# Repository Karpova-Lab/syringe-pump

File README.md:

# !!! Please see an updated version of this pump at https://www.github.com/Karpova-Lab/syringe-pump !!!

# Open Syringe Pump

- Full documentation: [https://karpova-lab.github.io/syringe-pump/v3.0/](https://karpova-lab.github.io/syringe-pump/v3.0/)
- Demo video: [https://vimeo.com/543307158](https://vimeo.com/543307158)
- The design of this pump has been updated to use some 3D printed parts. This results in fewer parts, faster/easier assembly, and a stiffer frame. The previous lasercut-only design is available on this repository's [lasercut_frame branch](https://github.com/Karpova-Lab/syringe-pump/tree/lasercut_frame).

# Features
- Push and pull capable
- Small footprint (33 cm x 14 cm x 10 cm)
- Can be mounted vertically to [DIN rail](https://duckduckgo.com/?q=DIN+rail&t=hc&va=u&iax=images&ia=images)
- Modular electronics can be swapped in and out to be compatible with whatever system you choose
- Cost ~$200
- Assembly time ~15 minutes

## Demo Video

<a target="_blank" href="https://vimeo.com/543307158">
    </img>
</a>

## Diagram

## Render

### Pump
Small footprint operate horizontally or be mounted vertically to DIN rail

<a href="readme_media/vertical_render.gif">
  
  </img>
</a>
<a href="readme_media/iso_views.png">
  
  </img>
</a>

### Modular motor controller
Swap out the motor controller to make upgrades or add compatibility with various systems.

</img>

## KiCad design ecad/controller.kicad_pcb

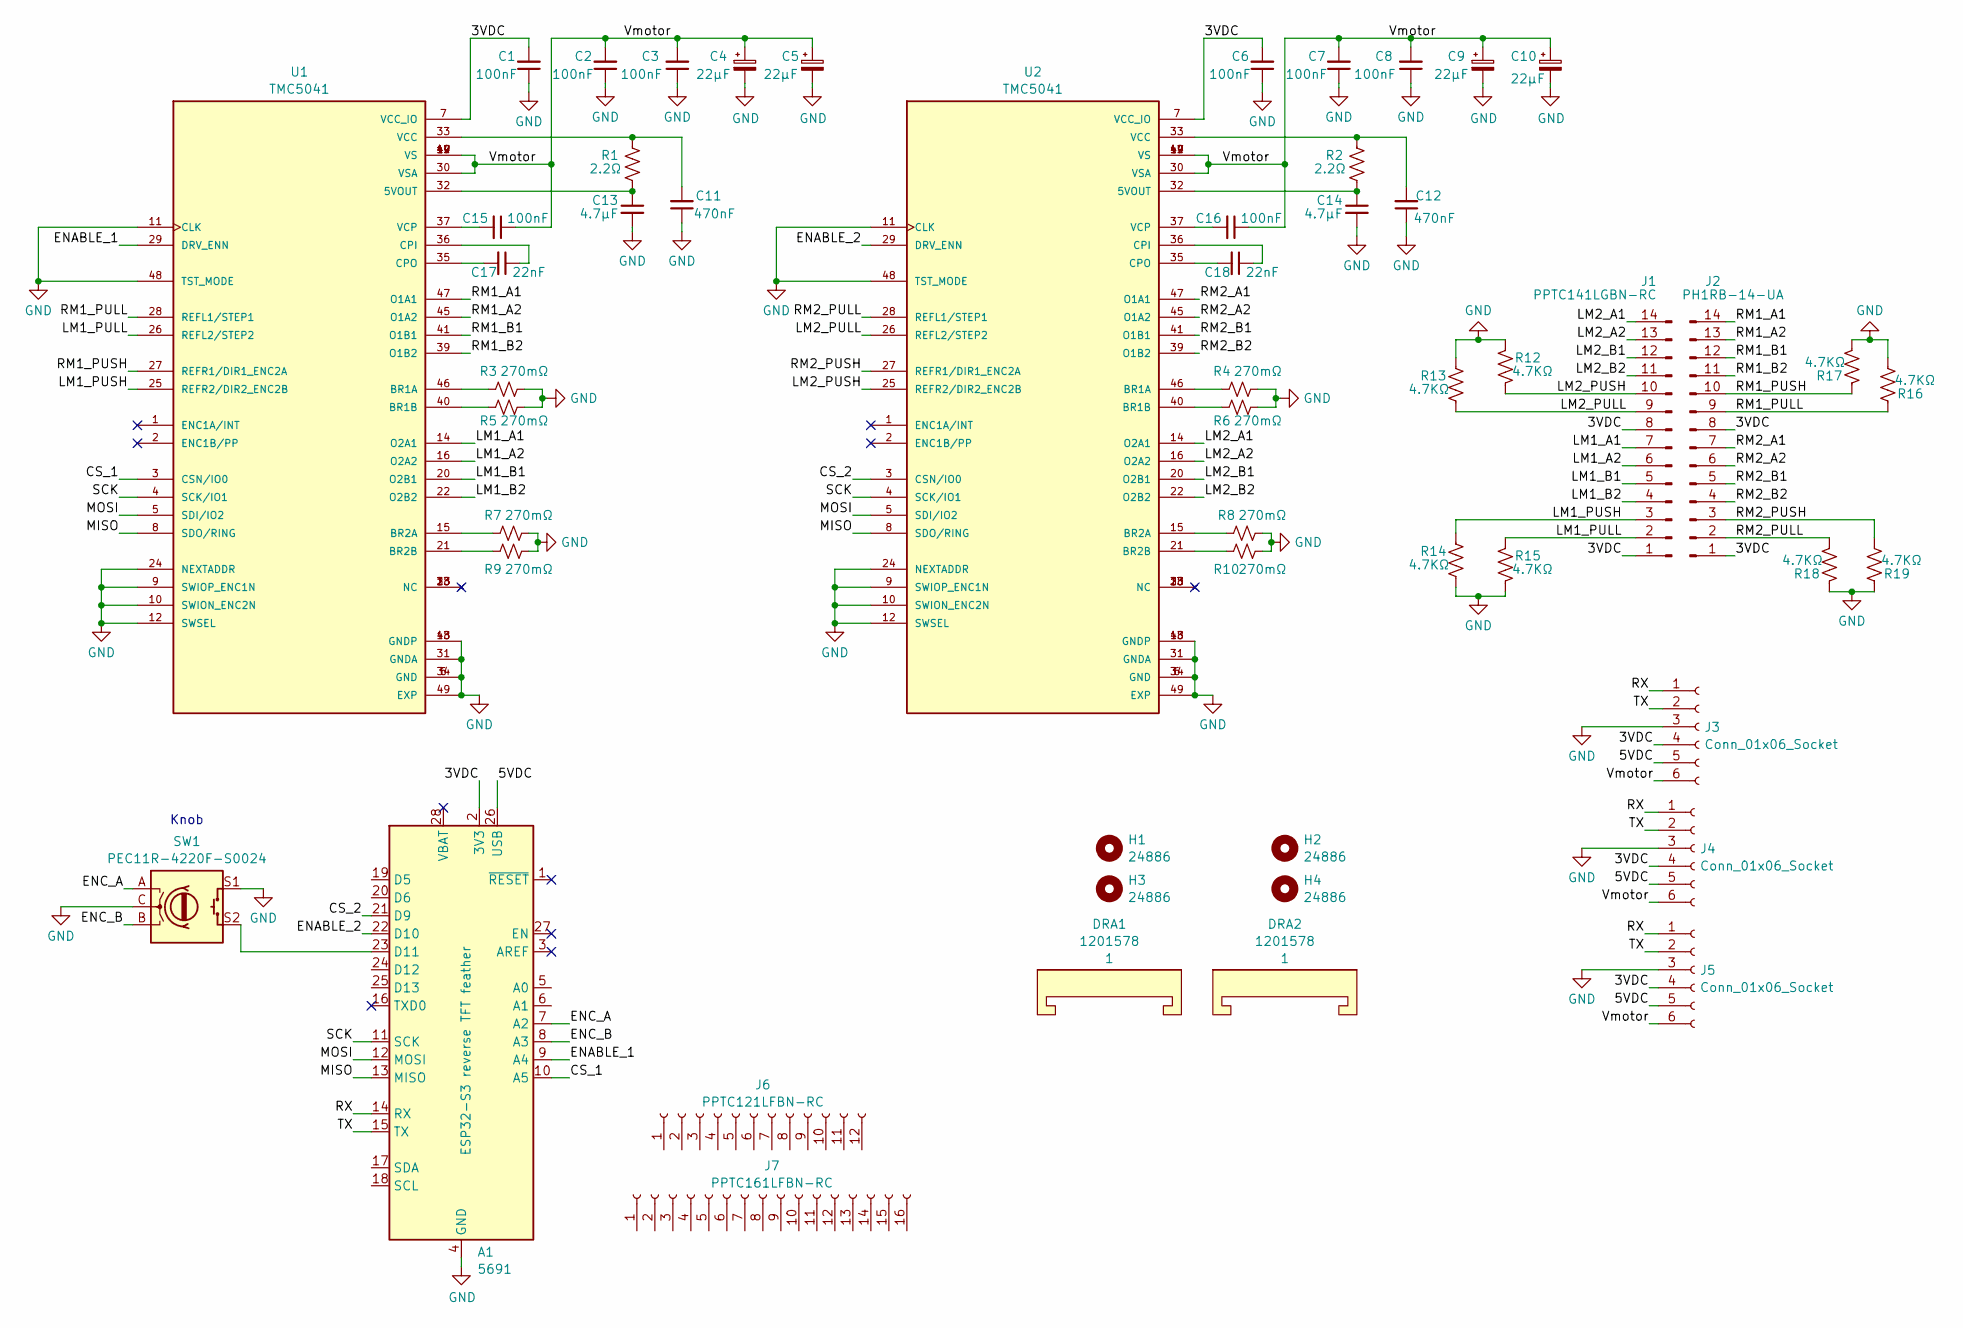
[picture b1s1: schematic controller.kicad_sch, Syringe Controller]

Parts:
A1: 5691; Adafruit_Feather
C1, C2, C3, C6, C7, C8, C15, C16: 100nF; C_0603_1608Metric
C4, C5, C9, C10: 22µF; C_1206_3216Metric
C11, C12: 470nF; C_0603_1608Metric
C13, C14: 4.7µF; C_0603_1608Metric
C17, C18: 22nF; C_0603_1608Metric
DRA1, DRA2: 1201578; DIN_Clip
H1, H2, H3, H4: 24886; standoff_nut
J1: PPTC141LGBN-RC; PinSocket_1x14_P2.54mm_Horizontal
J2: PH1RB-14-UA; PinHeader_1x14_P2.54mm_Horizontal
J3, J4, J5: Conn_01x06_Socket; PinHeader_1x06_P2.54mm_Vertical
J6: PPTC121LFBN-RC
J7: PPTC161LFBN-RC
R1, R2: 2.2Ω; R_0603_1608Metric
R3, R4, R5, R6, R7, R8, R9, R10: 270mΩ; R_1206_3216Metric
R12, R13, R14, R15, R16, R17, R18, R19: 4.7KΩ; R_0603_1608Metric
SW1: PEC11R-4220F-S0024; encoder_PEC11R
U1, U2: TMC5041; TMC_5072

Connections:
/3VDC: A1.2 (3V3), C1.2, C6.2, J1.1, J1.8, J2.1, J2.8, J3.4, J4.4, J5.4, U1.7 (VCC_IO), U2.7 (VCC_IO)
/5VDC: A1.26 (USB), J3.5, J4.5, J5.5
/CS_1: A1.10 (A5), U1.3 (CSN/IO0)
/CS_2: A1.21 (D9), U2.3 (CSN/IO0)
/ENABLE_1: A1.9 (A4), U1.29 (DRV_ENN)
/ENABLE_2: A1.22 (D10), U2.29 (DRV_ENN)
/ENC_A: A1.7 (A2), SW1.A
/ENC_B: A1.8 (A3), SW1.B
/LM1_A1: J1.7, U1.14 (O2A1)
/LM1_A2: J1.6, U1.16 (O2A2)
/LM1_B1: J1.5, U1.20 (O2B1)
/LM1_B2: J1.4, U1.22 (O2B2)
/LM1_PULL: J1.2, R15.1, U1.26 (REFL2/STEP2)
/LM1_PUSH: J1.3, R14.1, U1.25 (REFR2/DIR2_ENC2B)
/LM2_A1: J1.14, U2.14 (O2A1)
/LM2_A2: J1.13, U2.16 (O2A2)
/LM2_B1: J1.12, U2.20 (O2B1)
/LM2_B2: J1.11, U2.22 (O2B2)
/LM2_PULL: J1.9, R13.2, U2.26 (REFL2/STEP2)
/LM2_PUSH: J1.10, R12.2, U2.25 (REFR2/DIR2_ENC2B)
/MISO: A1.13 (MISO), U1.8 (SDO/RING), U2.8 (SDO/RING)
/MOSI: A1.12 (MOSI), U1.5 (SDI/IO2), U2.5 (SDI/IO2)
/RM1_A1: J2.14, U1.47 (O1A1)
/RM1_A2: J2.13, U1.45 (O1A2)
/RM1_B1: J2.12, U1.41 (O1B1)
/RM1_B2: J2.11, U1.39 (O1B2)
/RM1_PULL: J2.9, R16.1, U1.28 (REFL1/STEP1)
/RM1_PUSH: J2.10, R17.1, U1.27 (REFR1/DIR1_ENC2A)
/RM2_A1: J2.7, U2.47 (O1A1)
/RM2_A2: J2.6, U2.45 (O1A2)
/RM2_B1: J2.5, U2.41 (O1B1)
/RM2_B2: J2.4, U2.39 (O1B2)
/RM2_PULL: J2.2, R18.2, U2.28 (REFL1/STEP1)
/RM2_PUSH: J2.3, R19.2, U2.27 (REFR1/DIR1_ENC2A)
/RX: A1.14 (RX), J3.1, J4.1, J5.1
/SCK: A1.11 (SCK), U1.4 (SCK/IO1), U2.4 (SCK/IO1)
/TX: A1.15 (TX), J3.2, J4.2, J5.2
/Vmotor: C2.2, C3.2, C4.1, C5.1, C7.2, C8.2, C9.1, C10.1, C15.1, C16.1, J3.6, J4.6, J5.6, U1.17 (VS), U1.19 (VS), U1.30 (VSA), U1.42 (VS), U1.44 (VS), U2.17 (VS), U2.19 (VS), U2.30 (VSA), U2.42 (VS), U2.44 (VS)
GND: A1.4 (GND), C1.1, C2.1, C3.1, C4.2, C5.2, C6.1, C7.1, C8.1, C9.2, C10.2, C11.1, C12.1, C13.2, C14.2, J3.3, J4.3, J5.3, R3.2, R4.2, R5.1, R6.1, R7.2, R8.2, R9.1, R10.1, R12.1, R13.1, R14.2, R15.2, R16.2, R17.2, R18.1, R19.1, SW1.C, SW1.S1, U1.6 (GND), U1.9 (SWIOP_ENC1N), U1.10 (SWION_ENC2N), U1.11 (CLK), U1.12 (SWSEL), U1.18 (GNDP), U1.24 (NEXTADDR), U1.31 (GNDA), U1.34 (GND), U1.43 (GNDP), U1.48 (TST_MODE), U1.49 (EXP), U2.6 (GND), U2.9 (SWIOP_ENC1N), U2.10 (SWION_ENC2N), U2.11 (CLK), U2.12 (SWSEL), U2.18 (GNDP), U2.24 (NEXTADDR), U2.31 (GNDA), U2.34 (GND), U2.43 (GNDP), U2.48 (TST_MODE), U2.49 (EXP)
unnamed: A1.23 (D11), SW1.S2
unnamed: C13.1, R1.2, U1.32 (5VOUT)
unnamed: R3.1, U1.46 (BR1A)
unnamed: R5.2, U1.40 (BR1B)
unnamed: R7.1, U1.15 (BR2A)
unnamed: R9.2, U1.21 (BR2B)
unnamed: C17.1, U1.36 (CPI)
unnamed: C17.2, U1.35 (CPO)
unnamed: C11.2, R1.1, U1.33 (VCC)
unnamed: C15.2, U1.37 (VCP)
unnamed: C14.1, R2.2, U2.32 (5VOUT)
unnamed: R4.1, U2.46 (BR1A)
unnamed: R6.2, U2.40 (BR1B)
unnamed: R8.1, U2.15 (BR2A)
unnamed: R10.2, U2.21 (BR2B)
unnamed: C18.1, U2.36 (CPI)
unnamed: C18.2, U2.35 (CPO)
unnamed: C12.2, R2.1, U2.33 (VCC)
unnamed: C16.2, U2.37 (VCP)

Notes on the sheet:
Knob

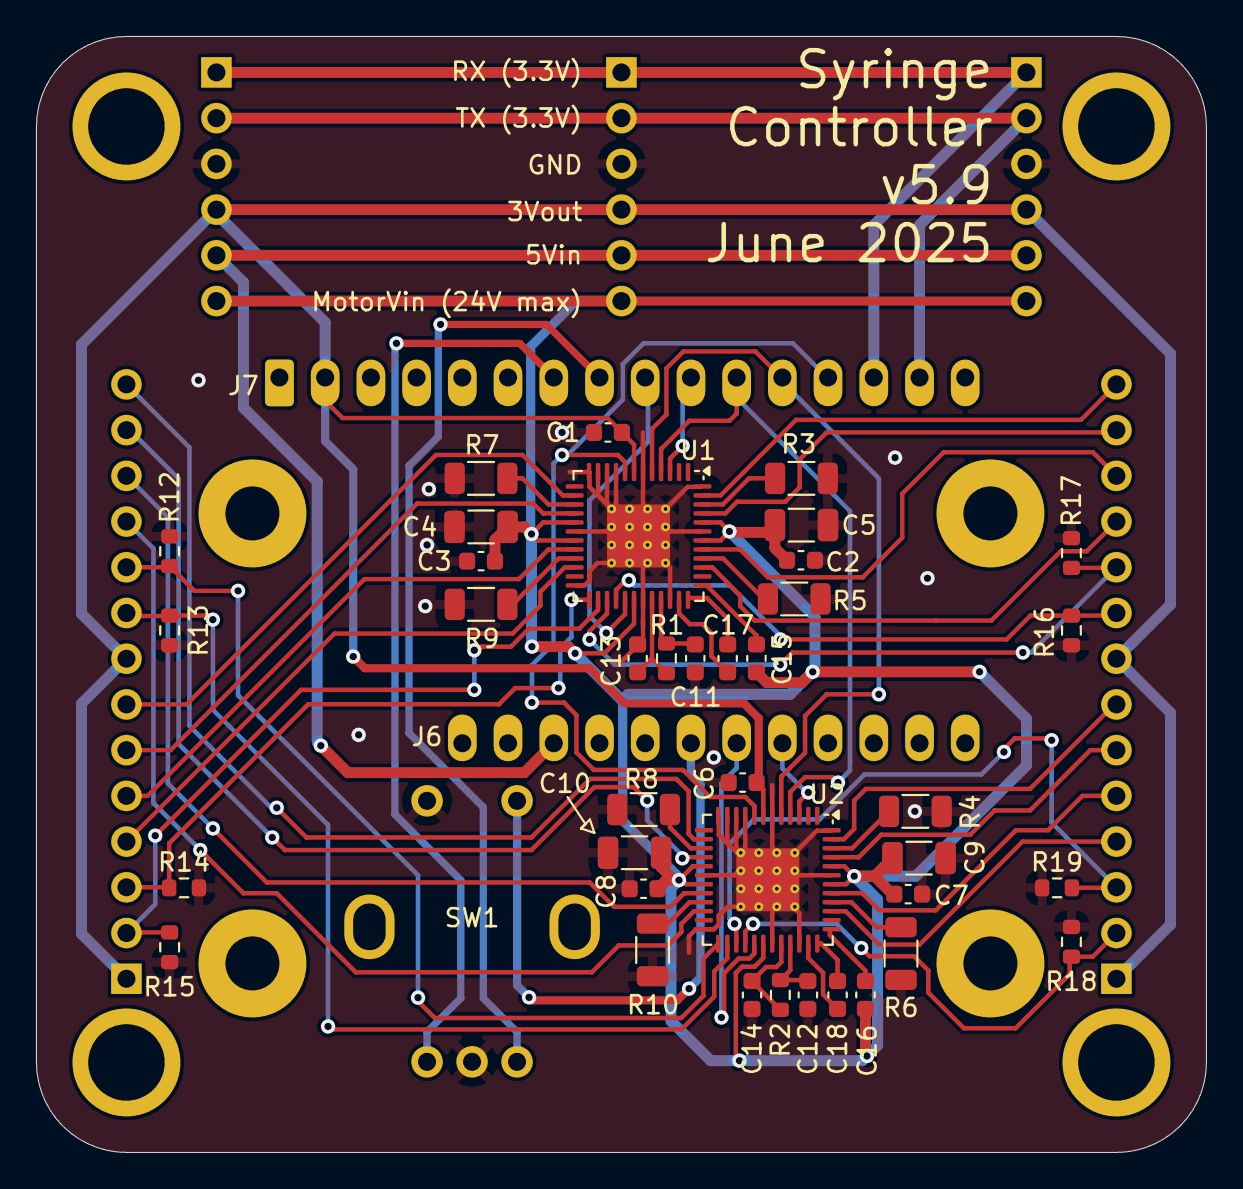
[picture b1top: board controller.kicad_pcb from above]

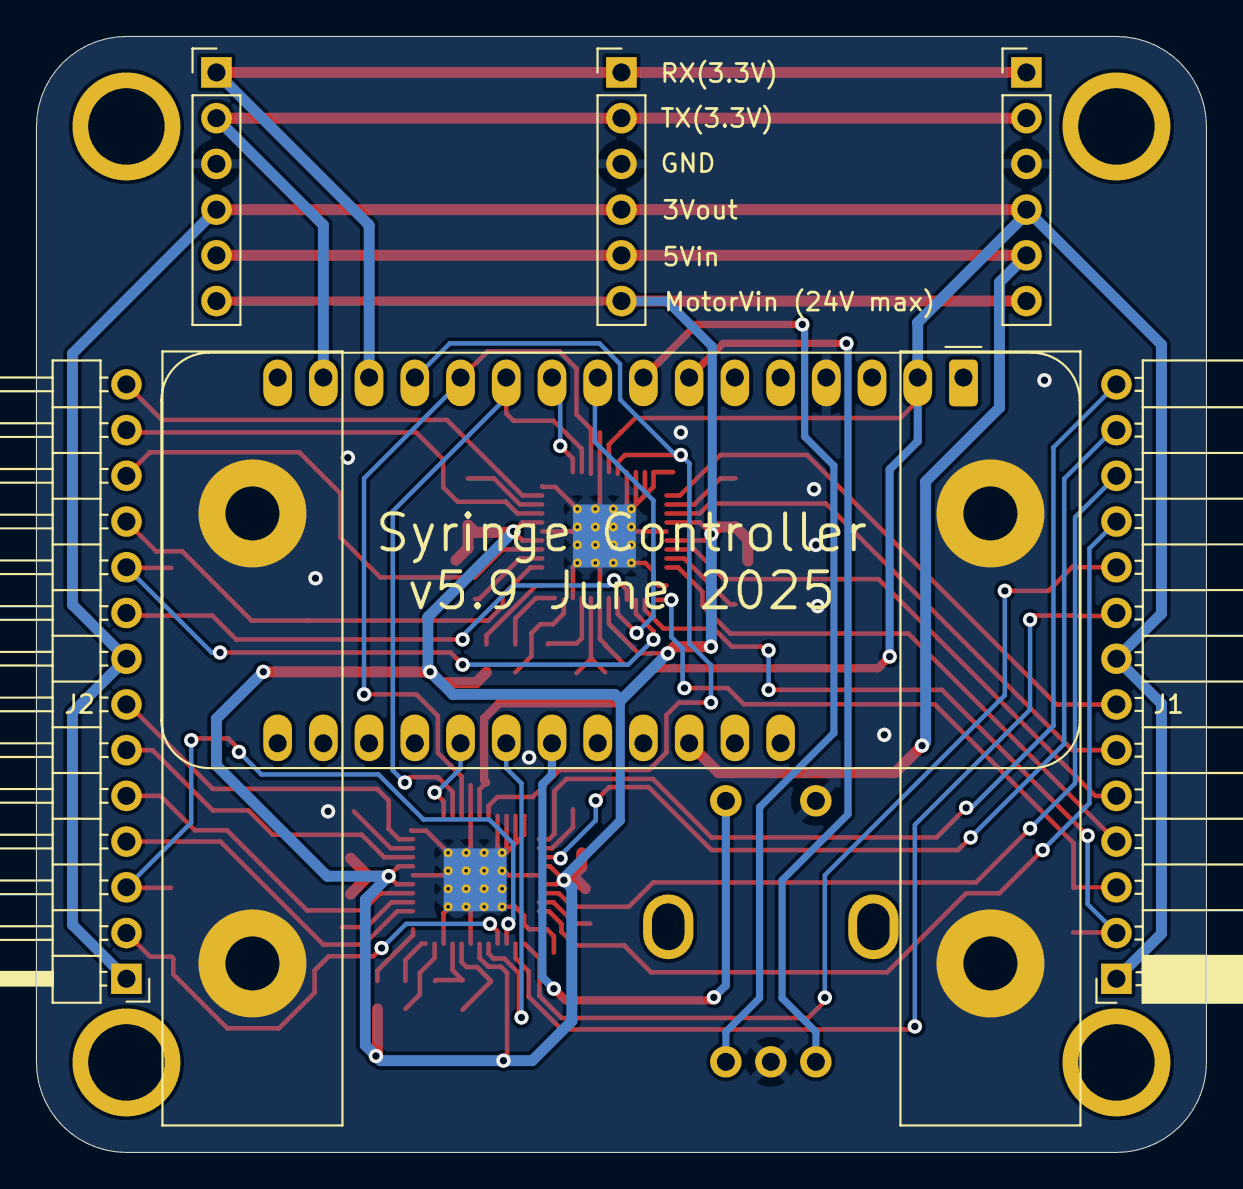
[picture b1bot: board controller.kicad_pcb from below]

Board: 2 copper layers, 65.0 x 62.0 mm, 51 parts (6 on the bottom side), 58 nets.

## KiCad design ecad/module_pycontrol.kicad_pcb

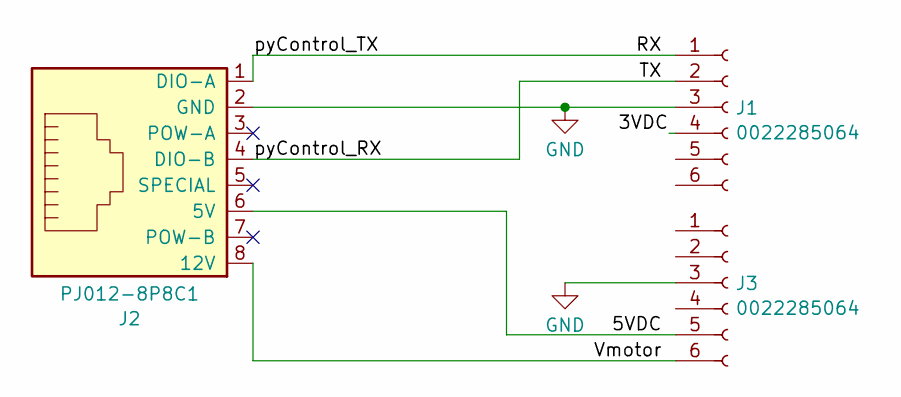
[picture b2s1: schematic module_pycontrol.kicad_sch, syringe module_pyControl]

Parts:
J1, J3: 0022285064; PinHeader_1x06_P2.54mm_Vertical
J2: PJ012-8P8C1; RJ45_TH_Vertical_PJ012

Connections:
/3VDC: J1.4
/5VDC: J2.6 (5V), J3.5
/RX: J1.1, J2.1 (DIO-A)
/TX: J1.2, J2.4 (DIO-B)
/Vmotor: J2.8 (12V), J3.6
GND: J1.3, J2.2 (GND), J3.3

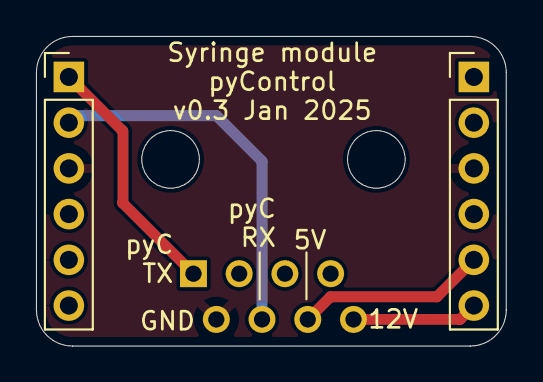
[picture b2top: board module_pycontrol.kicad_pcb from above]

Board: 2 copper layers, 26.1 x 17.2 mm, 3 parts (1 on the bottom side), 5 nets.

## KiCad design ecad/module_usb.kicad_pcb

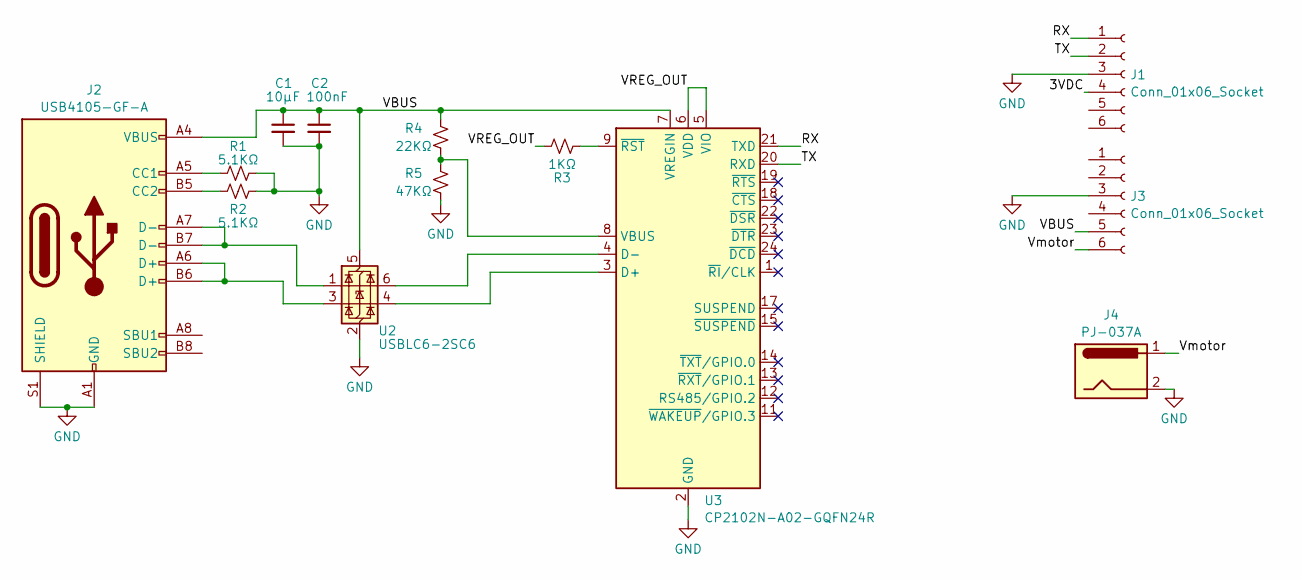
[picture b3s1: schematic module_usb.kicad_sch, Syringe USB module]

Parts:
C1: 10µF; C_0805_2012Metric
C2: 100nF; C_0805_2012Metric
J1, J3: Conn_01x06_Socket; PinHeader_1x06_P2.54mm_Vertical
J2: USB4105-GF-A; USB_C_Receptacle_GCT_USB4105-xx-A_16P_TopMnt_Horizontal
J4: PJ-037A; DC_Jack
R1, R2: 5.1KΩ; R_0805_2012Metric
R3: 1KΩ; R_0805_2012Metric
R4: 22KΩ; R_0805_2012Metric
R5: 47KΩ; R_0805_2012Metric
U2: USBLC6-2SC6; SOT-23-6
U3: CP2102N-A02-GQFN24R; QFN-24-1EP_4x4mm_P0.5mm_EP2.6x2.6mm

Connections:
/3VDC: J1.4
/RX: J1.1, U3.21 (TXD)
/TX: J1.2, U3.20 (RXD)
/VBUS: C1.1, C2.1, J2.A4 (VBUS), J2.A9 (VBUS), J2.B4 (VBUS), J2.B9 (VBUS), J3.5, R4.2, U2.5 (VBUS), U3.7 (VREGIN)
/VREG_OUT: R3.2, U3.5 (VIO), U3.6 (VDD)
/Vmotor: J3.6, J4.1
GND: C1.2, C2.2, J1.3, J2.A1 (GND), J2.A12 (GND), J2.B1 (GND), J2.B12 (GND), J2.S1 (SHIELD), J3.3, J4.2, R1.2, R2.1, R5.1, U2.2 (GND), U3.2 (GND), U3.25 (GND)
unnamed: J2.A5 (CC1), R1.1
unnamed: J2.B5 (CC2), R2.2
unnamed: J2.A6 (D+), J2.B6 (D+), U2.3 (I/O2)
unnamed: J2.A7 (D-), J2.B7 (D-), U2.1 (I/O1)
unnamed: U2.4 (I/O2), U3.3 (D+)
unnamed: U2.6 (I/O1), U3.4 (D-)
unnamed: R4.1, R5.2, U3.8 (VBUS)
unnamed: R3.1, U3.9 (~RST)

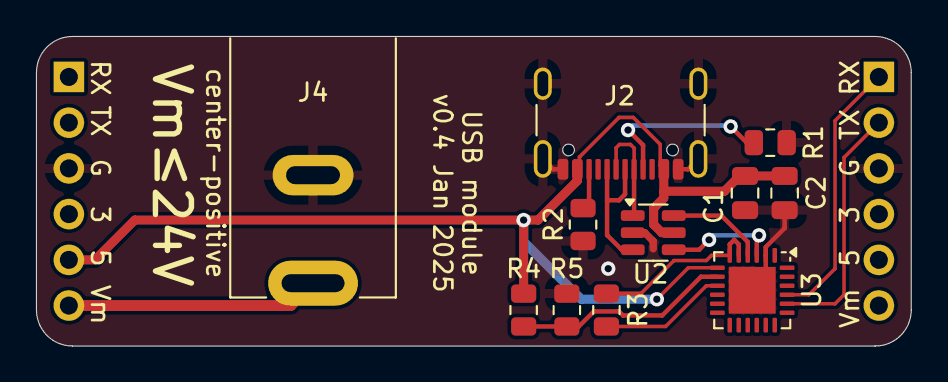
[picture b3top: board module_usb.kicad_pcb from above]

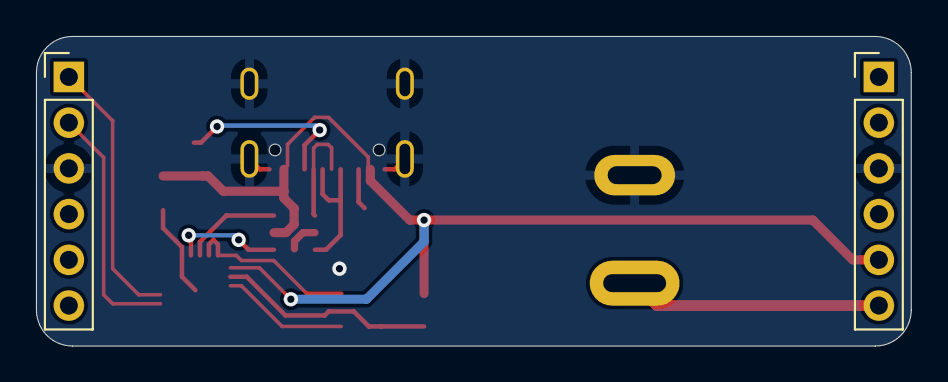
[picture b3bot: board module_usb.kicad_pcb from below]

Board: 2 copper layers, 48.6 x 17.2 mm, 13 parts (2 on the bottom side), 14 nets.

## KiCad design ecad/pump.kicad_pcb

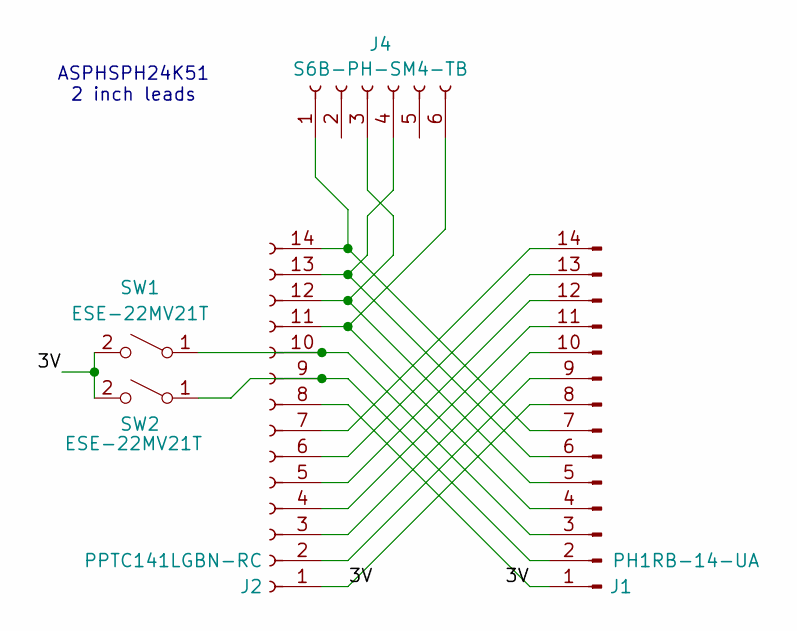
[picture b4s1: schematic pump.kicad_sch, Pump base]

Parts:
J1: PH1RB-14-UA; PinHeader_1x14_P2.54mm_Horizontal
J2: PPTC141LGBN-RC; PinSocket_1x14_P2.54mm_Horizontal
J4: S6B-PH-SM4-TB; JST_PH_S6B-PH-SM4-TB_1x06-1MP_P2.00mm_Horizontal
SW1, SW2: ESE-22MV21T; SW_ESE-22MV21T

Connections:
/3V: J1.1, J1.8, J2.1, J2.8, SW1.2 (B), SW2.2 (B)
unnamed: J1.2, J2.9, SW2.1 (A)
unnamed: J1.3, J2.10, SW1.1 (A)
unnamed: J1.4, J2.11, J4.6
unnamed: J1.5, J2.12, J4.3
unnamed: J1.6, J2.13, J4.4
unnamed: J1.7, J2.14, J4.1
unnamed: J1.9, J2.2
unnamed: J1.10, J2.3
unnamed: J1.11, J2.4
unnamed: J1.12, J2.5
unnamed: J1.13, J2.6
unnamed: J1.14, J2.7

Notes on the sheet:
ASPHSPH24K51 2 inch leads

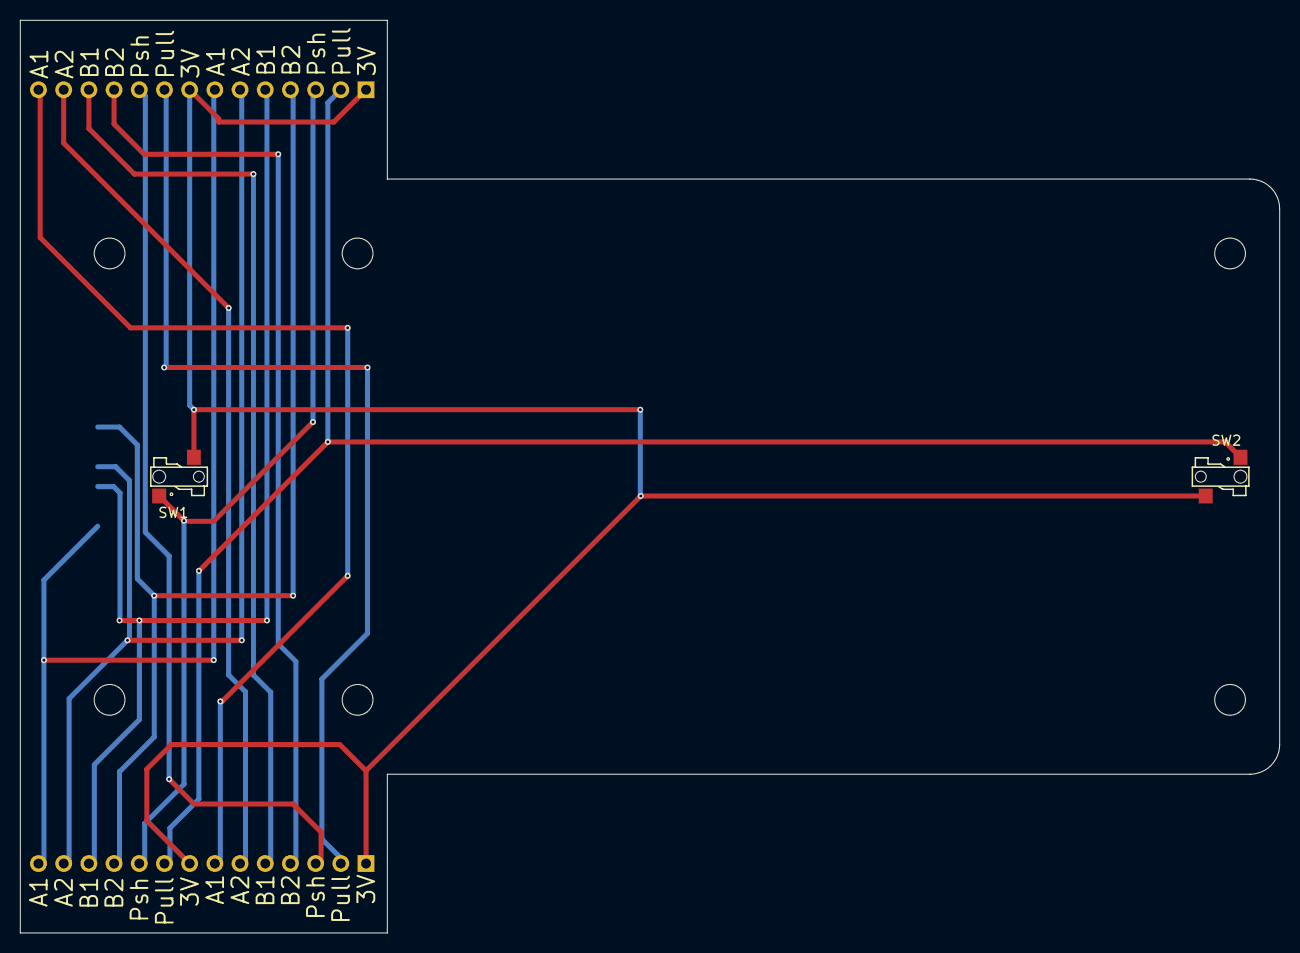
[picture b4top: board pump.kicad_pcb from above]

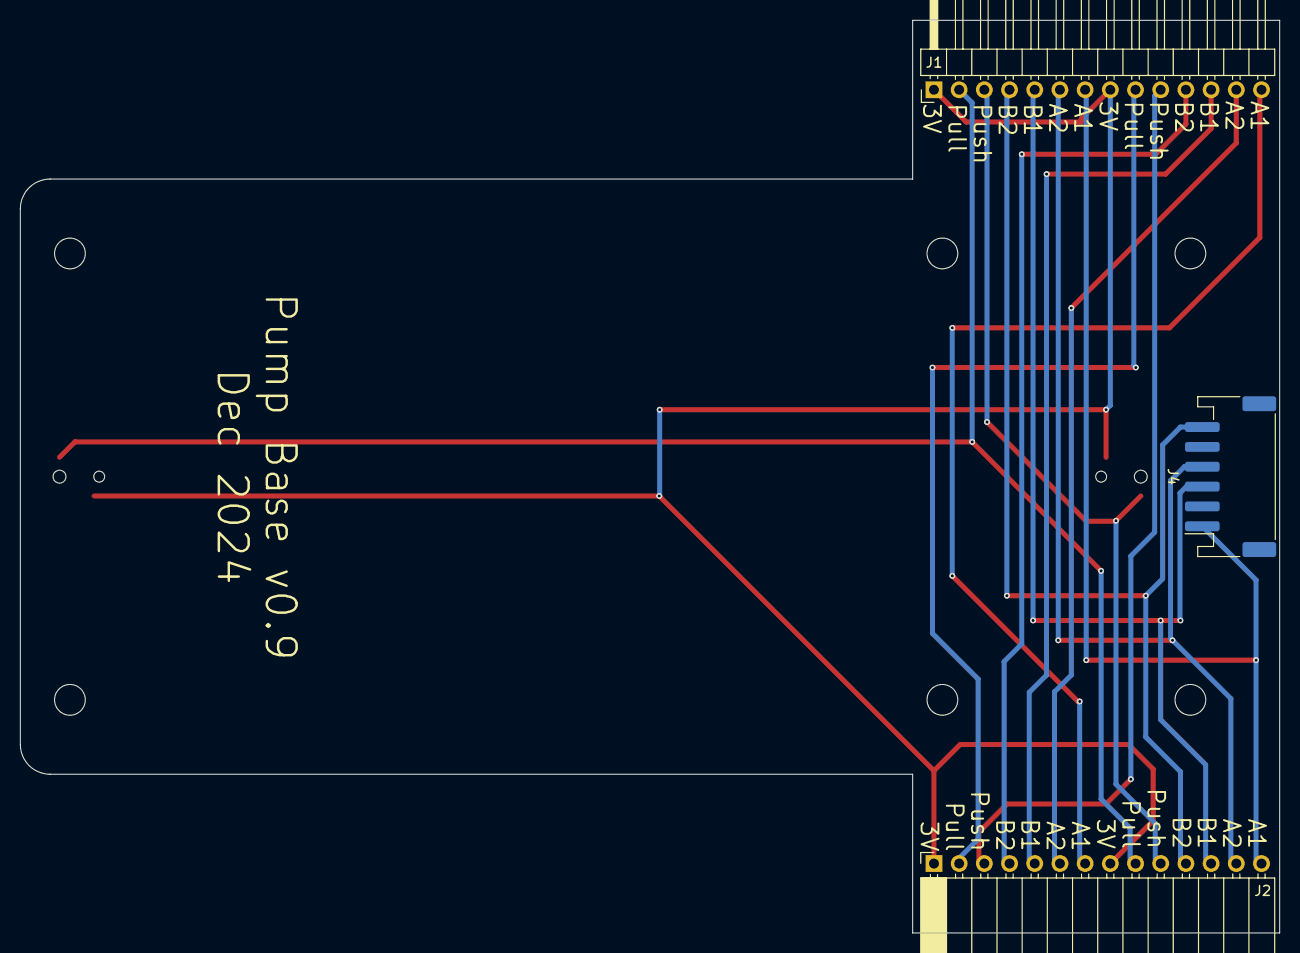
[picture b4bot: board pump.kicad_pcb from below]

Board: 2 copper layers, 126.9 x 92.0 mm, 5 parts (3 on the bottom side), 13 nets.

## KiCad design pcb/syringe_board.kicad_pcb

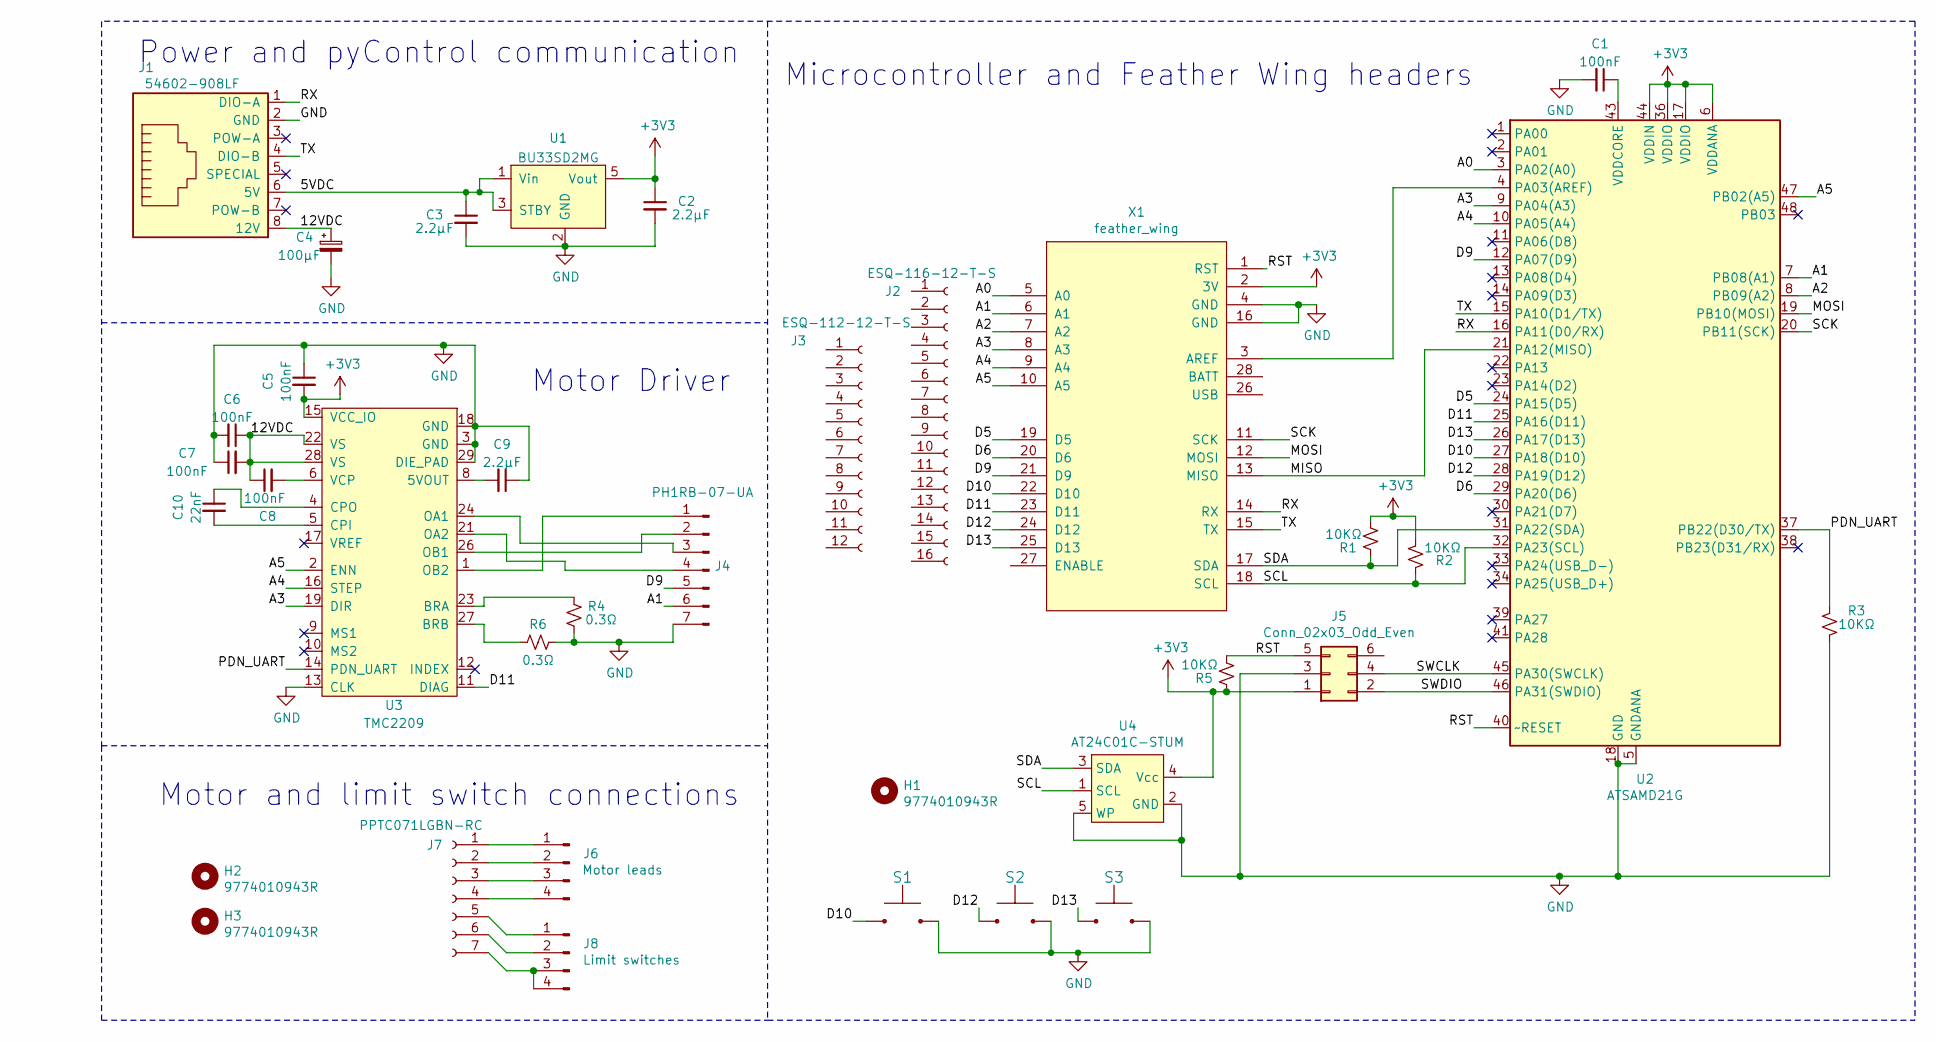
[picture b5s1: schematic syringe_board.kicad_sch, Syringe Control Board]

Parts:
C1, C5, C6, C7, C8: 100nF; C_0603_1608Metric
C2, C3, C9: 2.2µF; C_0603_1608Metric
C4: 100µF; CP_Elec_6.3x7.7
C10: 22nF; C_0603_1608Metric
H1, H2, H3: 9774010943R; standoff_nut
J1: 54602-908LF; RJ45_THP
J2: ESQ-116-12-T-S; PinSocket_1x16_P2.54mm_Vertical
J3: ESQ-112-12-T-S; PinSocket_1x12_P2.54mm_Vertical
J4: PH1RB-07-UA; PinHeader_1x07_P2.54mm_Horizontal
J5: Conn_02x03_Odd_Even; Tag-Connect_TC2030-IDC-NL_2x03_P1.27mm_Vertical
J6: Motor leads; PinHeader_2x02_P2.54mm_Vertical
J7: PPTC071LGBN-RC; PinSocket_1x07_P2.54mm_Horizontal
J8: Limit switches; PinHeader_2x02_P2.54mm_Vertical
R1, R2, R3, R5: 10KΩ; R_0603_1608Metric
R4, R6: 0.3Ω; R_0805_2012Metric
S1, S2, S3: PTS645VH39-2; SW_Tactile_SPST_Angled_PTS645Vx39-2LFS
U1: BU33SD2MG; SOT-23-5
U2: ATSAMD21G; TQFP-48_7x7mm_P0.5mm
U3: TMC2209; QFN-28-1EP_5x5mm_P0.5mm_EP3.35x3.35mm_ThermalVias
U4: AT24C01C-STUM; SOT-23-5
X1: feather_wing; Feather

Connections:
+3V3: C2.1, C5.2, J5.1, R1.1, R2.1, R5.2, U1.5 (Vout), U2.6 (VDDANA), U2.17 (VDDIO), U2.36 (VDDIO), U2.44 (VDDIN), U3.15 (VCC_IO), U4.4 (Vcc), X1.2 (3V)
/5VDC: C3.1, J1.6 (5V), U1.1 (Vin), U1.3 (STBY)
/12VDC: C4.1, C6.1, C7.2, C8.1, J1.8 (12V), U3.22 (VS), U3.28 (VS)
/A0: U2.3 (PA02(A0)), X1.5 (A0)
/A1: J4.6, U2.7 (PB08(A1)), X1.6 (A1)
/A2: U2.8 (PB09(A2)), X1.7 (A2)
/A3: U2.9 (PA04(A3)), U3.19 (DIR), X1.8 (A3)
/A4: U2.10 (PA05(A4)), U3.16 (STEP), X1.9 (A4)
/A5: U2.47 (PB02(A5)), U3.2 (ENN), X1.10 (A5)
/D5: U2.24 (PA15(D5)), X1.19 (D5)
/D6: U2.29 (PA20(D6)), X1.20 (D6)
/D9: J4.5, U2.12 (PA07(D9)), X1.21 (D9)
/D10: S1.1, U2.27 (PA18(D10)), X1.22 (D10)
/D11: U2.25 (PA16(D11)), U3.11 (DIAG), X1.23 (D11)
/D12: S2.1, U2.28 (PA19(D12)), X1.24 (D12)
/D13: S3.1, U2.26 (PA17(D13)), X1.25 (D13)
/MISO: U2.21 (PA12(MISO)), X1.13 (MISO)
/MOSI: U2.19 (PB10(MOSI)), X1.12 (MOSI)
/PDN_UART: R3.2, U2.37 (PB22(D30/TX)), U3.14 (PDN_UART)
/RST: J5.5, R5.1, U2.40 (~RESET), X1.1 (RST)
/RX: J1.1 (DIO-A), U2.16 (PA11(D0/RX)), X1.14 (RX)
/SCK: U2.20 (PB11(SCK)), X1.11 (SCK)
/SCL: R2.2, U2.32 (PA23(SCL)), U4.1 (SCL), X1.18 (SCL)
/SDA: R1.2, U2.31 (PA22(SDA)), U4.3 (SDA), X1.17 (SDA)
/SWCLK: J5.4, U2.45 (PA30(SWCLK))
/SWDIO: J5.2, U2.46 (PA31(SWDIO))
/TX: J1.4 (DIO-B), U2.15 (PA10(D1/TX)), X1.15 (TX)
GND: C1.2, C2.2, C3.2, C4.2, C5.1, C6.2, C7.1, C9.1, J1.2 (GND), J4.7, J5.3, R3.1, R4.2, R6.1, S1.2, S2.2, S3.2, U1.2 (GND), U2.5 (GNDANA), U2.18 (GND), U2.35 (GND), U2.42 (GND), U3.3 (GND), U3.13 (CLK), U3.18 (GND), U3.29 (DIE_PAD), U4.2 (GND), U4.5 (WP), X1.4 (GND), X1.16 (GND)
unnamed: C1.1, U2.43 (VDDCORE)
unnamed: C8.2, U3.6 (VCP)
unnamed: C9.2, U3.8 (5VOUT)
unnamed: C10.1, U3.4 (CPO)
unnamed: C10.2, U3.5 (CPI)
unnamed: J4.1, U3.1 (OB2)
unnamed: J4.2, U3.26 (OB1)
unnamed: J4.3, U3.24 (OA1)
unnamed: J4.4, U3.21 (OA2)
unnamed: J6.1, J7.1
unnamed: J6.2, J7.2
unnamed: J6.3, J7.3
unnamed: J6.4, J7.4
unnamed: J7.5, J8.1
unnamed: J7.6, J8.2
unnamed: J7.7, J8.3, J8.4
unnamed: R4.1, U3.23 (BRA)
unnamed: R6.2, U3.27 (BRB)
unnamed: U2.4 (PA03(AREF)), X1.3 (AREF)

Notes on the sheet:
Power and pyControl communication
Motor and limit switch connections
Motor Driver
Microcontroller and Feather Wing headers

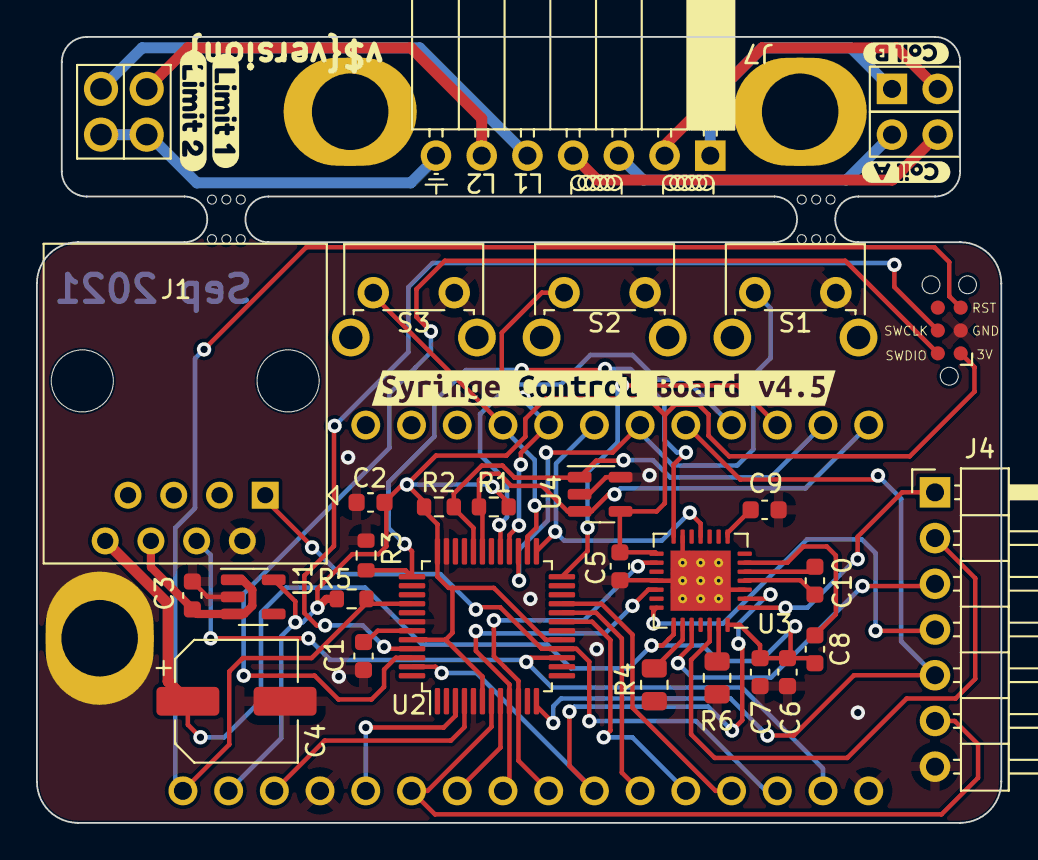
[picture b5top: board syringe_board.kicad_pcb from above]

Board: 2 copper layers, 53.6 x 43.7 mm, 40 parts (0 on the bottom side), 47 nets.

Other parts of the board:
MB1, MB2: VAL**; mouse-bite-2.54mm-slot
svg2mod, svg2mod#2, svg2mod#3, svg2mod#4, svg2mod#5: G***; svg2mod
